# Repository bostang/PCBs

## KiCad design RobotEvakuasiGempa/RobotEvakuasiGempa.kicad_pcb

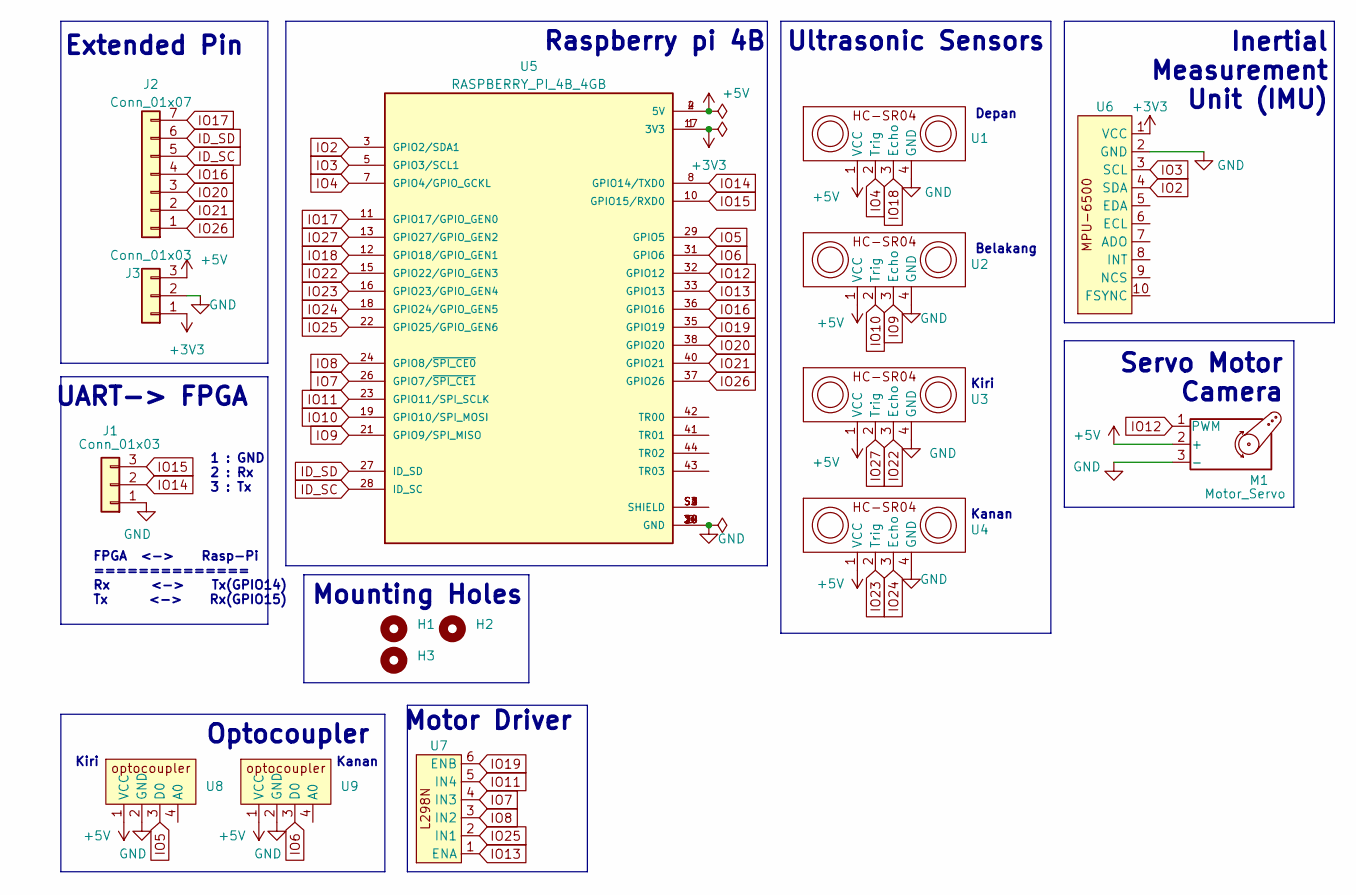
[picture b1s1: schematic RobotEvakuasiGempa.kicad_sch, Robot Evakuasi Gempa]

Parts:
H1, H2, H3: MountingHole; MountingHole_2.2mm_M2
J1, J3: Conn_01x03; PinHeader_1x03_P2.54mm_Vertical
J2: Conn_01x07; PinHeader_1x07_P2.54mm_Vertical
M1: Motor_Servo; PinHeader_1x03_P2.54mm_Vertical
U1, U2, U3, U4: JST_XH_B4B-XH-A_1x04_P2.50mm_Vertical
U5: RASPBERRY_PI_4B_4GB; MODULE_RASPBERRY_PI_4B_4GB_Flat_Ribbon_Cable; PARTREV 4
U6: MPU-6500
U7: L298N
U8, U9: Sensor Optocoupler

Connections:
+3V3: J3.1, U5.1 (3V3), U5.17 (3V3), U6.1 (VCC)
+5V: J3.3, M1.2 (+), U1.1 (VCC), U2.1 (VCC), U3.1 (VCC), U4.1 (VCC), U5.2 (5V), U5.4 (5V), U8.1 (VCC), U9.1 (VCC)
GND: J1.1, J3.2, M1.3 (-), U1.4 (GND), U2.4 (GND), U3.4 (GND), U4.4 (GND), U5.6 (GND), U5.9 (GND), U5.14 (GND), U5.20 (GND), U5.25 (GND), U5.30 (GND), U5.34 (GND), U5.39 (GND), U6.2 (GND), U8.2 (GND), U9.2 (GND)
ID_SC: J2.5, U5.28 (ID_SC)
ID_SD: J2.6, U5.27 (ID_SD)
IO2: U5.3 (GPIO2/SDA1), U6.4 (SDA)
IO3: U5.5 (GPIO3/SCL1), U6.3 (SCL)
IO4: U1.2 (Trig), U5.7 (GPIO4/GPIO_GCKL)
IO5: U5.29 (GPIO5), U8.3 (D0)
IO6: U5.31 (GPIO6), U9.3 (D0)
IO7: U5.26 (GPIO7/~SPI_CE1), U7.4 (IN3)
IO8: U5.24 (GPIO8/~SPI_CE0), U7.3 (IN2)
IO9: U2.3 (Echo), U5.21 (GPIO9/SPI_MISO)
IO10: U2.2 (Trig), U5.19 (GPIO10/SPI_MOSI)
IO11: U5.23 (GPIO11/SPI_SCLK), U7.5 (IN4)
IO12: M1.1 (PWM), U5.32 (GPIO12)
IO13: U5.33 (GPIO13), U7.1 (ENA)
IO14: J1.2, U5.8 (GPIO14/TXD0)
IO15: J1.3, U5.10 (GPIO15/RXD0)
IO16: J2.4, U5.36 (GPIO16)
IO17: J2.7, U5.11 (GPIO17/GPIO_GEN0)
IO18: U1.3 (Echo), U5.12 (GPIO18/GPIO_GEN1)
IO19: U5.35 (GPIO19), U7.6 (ENB)
IO20: J2.3, U5.38 (GPIO20)
IO21: J2.2, U5.40 (GPIO21)
IO22: U3.3 (Echo), U5.15 (GPIO22/GPIO_GEN3)
IO23: U4.2 (Trig), U5.16 (GPIO23/GPIO_GEN4)
IO24: U4.3 (Echo), U5.18 (GPIO24/GPIO_GEN5)
IO25: U5.22 (GPIO25/GPIO_GEN6), U7.2 (IN1)
IO26: J2.1, U5.37 (GPIO26)
IO27: U3.2 (Trig), U5.13 (GPIO27/GPIO_GEN2)

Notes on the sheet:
1 : GND 2 : Rx 3 : Tx
Servo Motor Camera
Mounting Holes
Depan
FPGA <-> Rasp-Pi ============== Rx <-> Tx(GPIO14) Tx <-> Rx(GPIO15)
Kiri
Raspberry pi 4B
UART-> FPGA
Ultrasonic Sensors
Belakang
Motor Driver
Inertial Measurement Unit (IMU)
Kanan
Extended Pin
Optocoupler

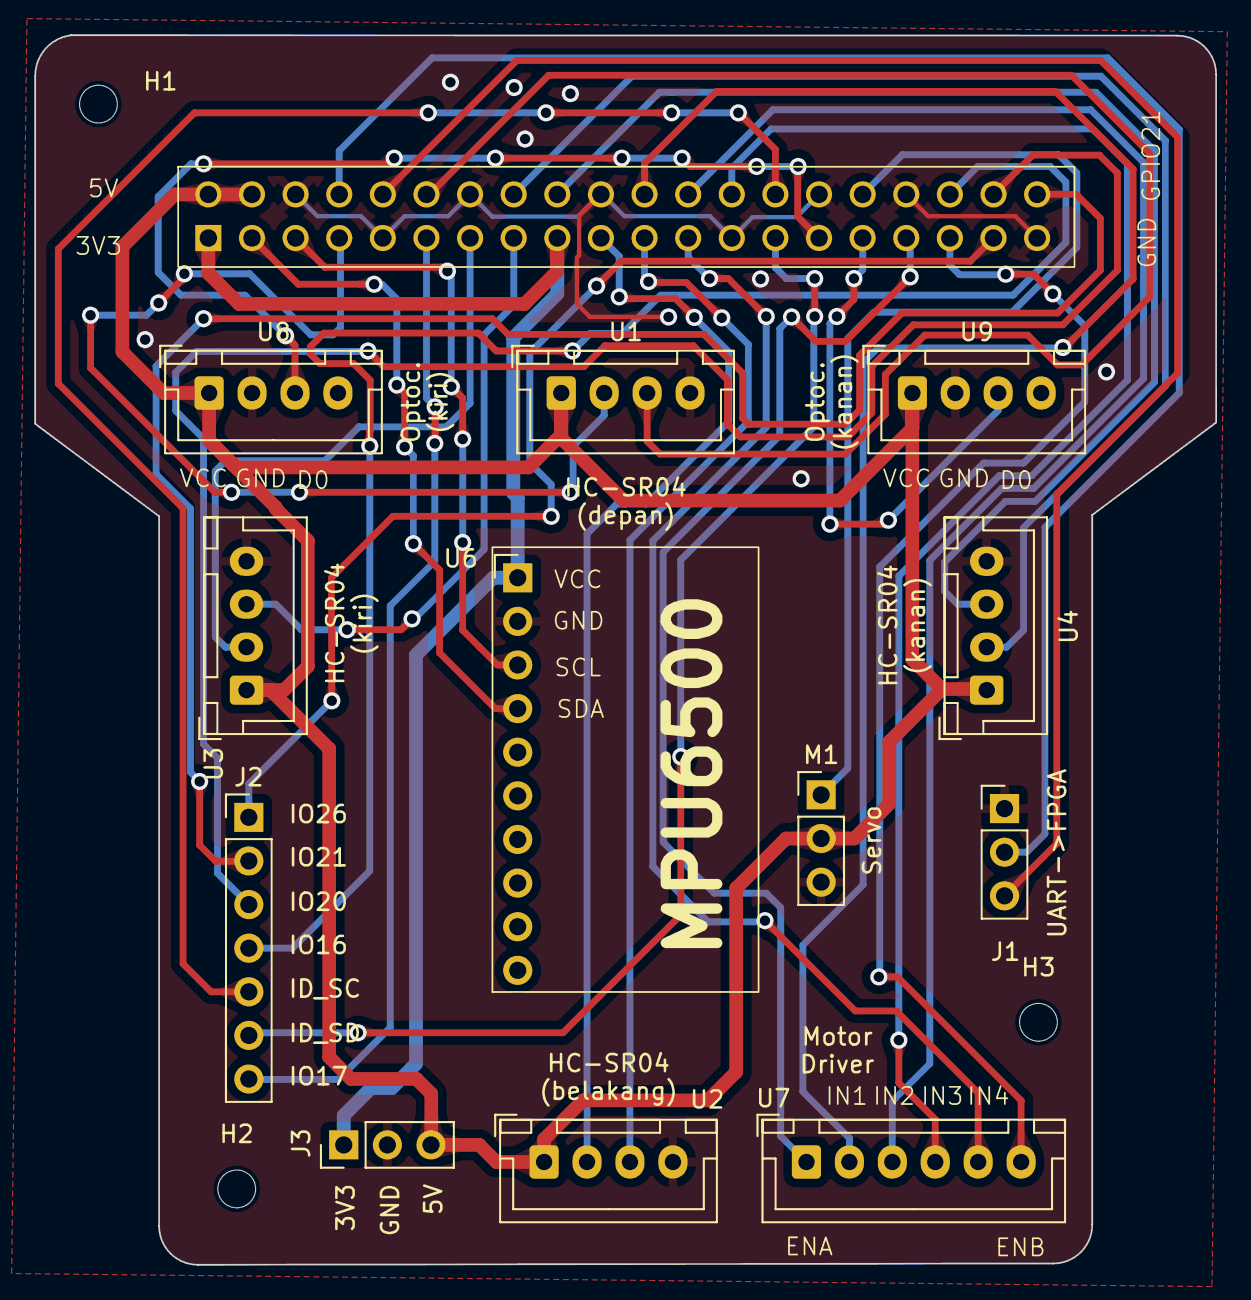
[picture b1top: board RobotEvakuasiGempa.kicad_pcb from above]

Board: 2 copper layers, 68.8 x 71.6 mm, 16 parts (0 on the bottom side), 31 nets.

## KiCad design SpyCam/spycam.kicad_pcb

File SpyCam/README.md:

# Spycam

Sebuah kamera pengintai berbasis ESP-32 camera yang berbentuk sebuah kalung.

# Skematik

# Tampilan

## Tampak Atas

## Tampak Bawah

## Bird-view

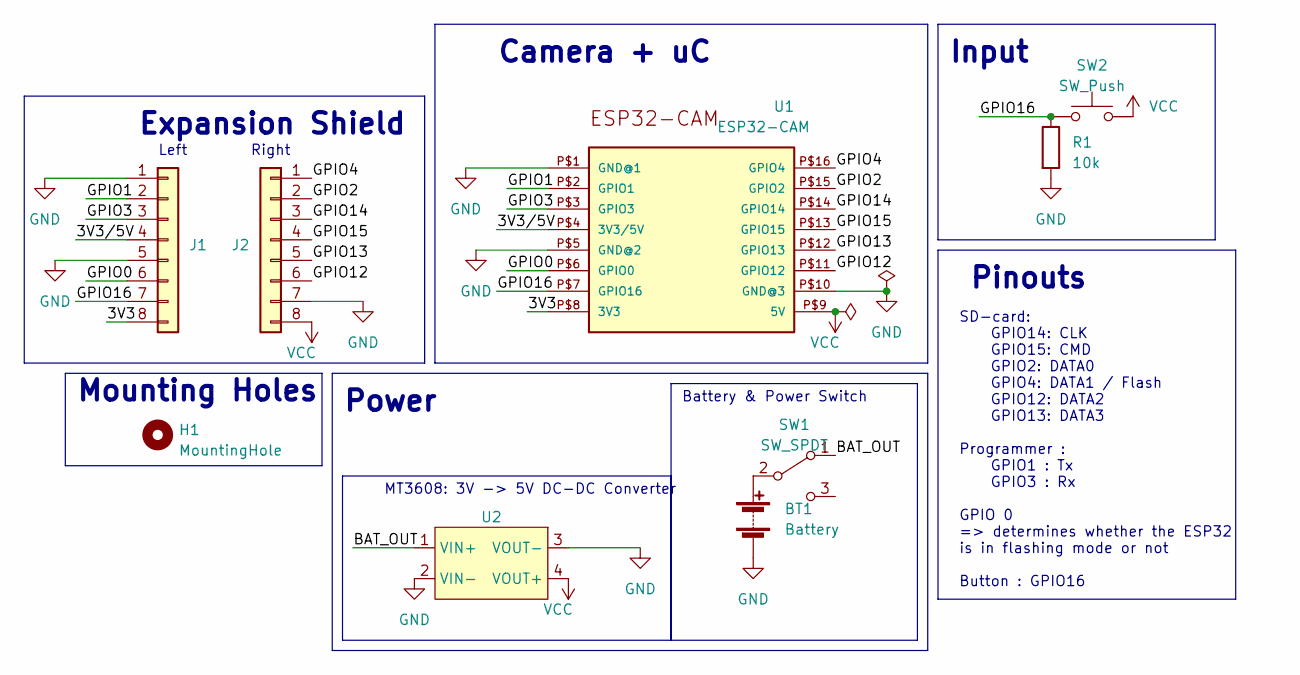
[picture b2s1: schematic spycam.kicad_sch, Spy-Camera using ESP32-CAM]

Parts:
BT1: Battery; BatteryHolder_Keystone_103_1x20mm
H1: MountingHole; MountingHole_3.2mm_M3
J1, J2: Conn_01x08; PinHeader_1x08_P2.54mm_Vertical
R1: 10k; R_1206_3216Metric
SW1: SW_SPDT; SW_E-Switch_EG1224_SPDT_Angled
SW2: SW_Push; SW_PUSH-12mm
U1: ESP32-CAM
U2: MT3608_module_v2

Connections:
/3V3: J1.8, U1.P$8 (3V3)
/3V3/5V: J1.4, U1.P$4 (3V3/5V)
/BAT_OUT: SW1.1 (A), U2.1 (VIN+)
/GPIO0: J1.6, U1.P$6 (GPIO0)
/GPIO1: J1.2, U1.P$2 (GPIO1)
/GPIO2: J2.2, U1.P$15 (GPIO2)
/GPIO3: J1.3, U1.P$3 (GPIO3)
/GPIO4: J2.1, U1.P$16 (GPIO4)
/GPIO12: J2.6, U1.P$11 (GPIO12)
/GPIO13: J2.5, U1.P$12 (GPIO13)
/GPIO14: J2.3, U1.P$14 (GPIO14)
/GPIO15: J2.4, U1.P$13 (GPIO15)
/GPIO16: J1.7, R1.1, SW2.1, U1.P$7 (GPIO16)
GND: BT1.2 (-), J1.1, J1.5, J2.7, R1.2, U1.P$1 (GND@1), U1.P$5 (GND@2), U1.P$10 (GND@3), U2.2 (VIN-), U2.3 (VOUT-)
unnamed: BT1.1 (+), SW1.2 (B)
VCC: J2.8, SW2.2, U1.P$9 (5V), U2.4 (VOUT+)

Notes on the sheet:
Expansion Shield
MT3608: 3V -> 5V DC-DC Converter
Pinouts
Battery & Power Switch
Right
Left
SD-card: GPIO14: CLK GPIO15: CMD GPIO2: DATA0 GPIO4: DATA1 / Flash GPIO12: DATA2 GPIO13: DATA3 Programmer : GPIO1 : Tx GPIO3 : Rx GPIO 0 => determines whether the ESP32 is in flashing mode or not Button : GPIO16
Mounting Holes
Camera + uC
Input
Power

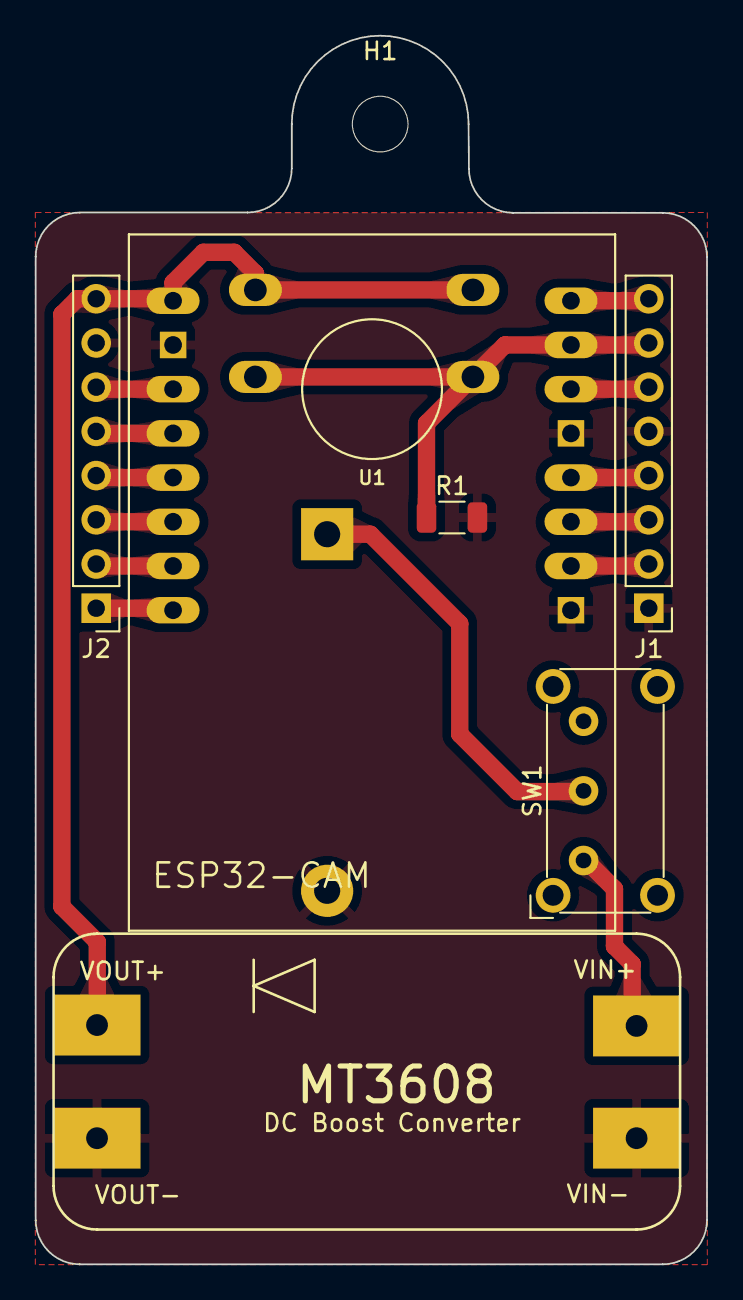
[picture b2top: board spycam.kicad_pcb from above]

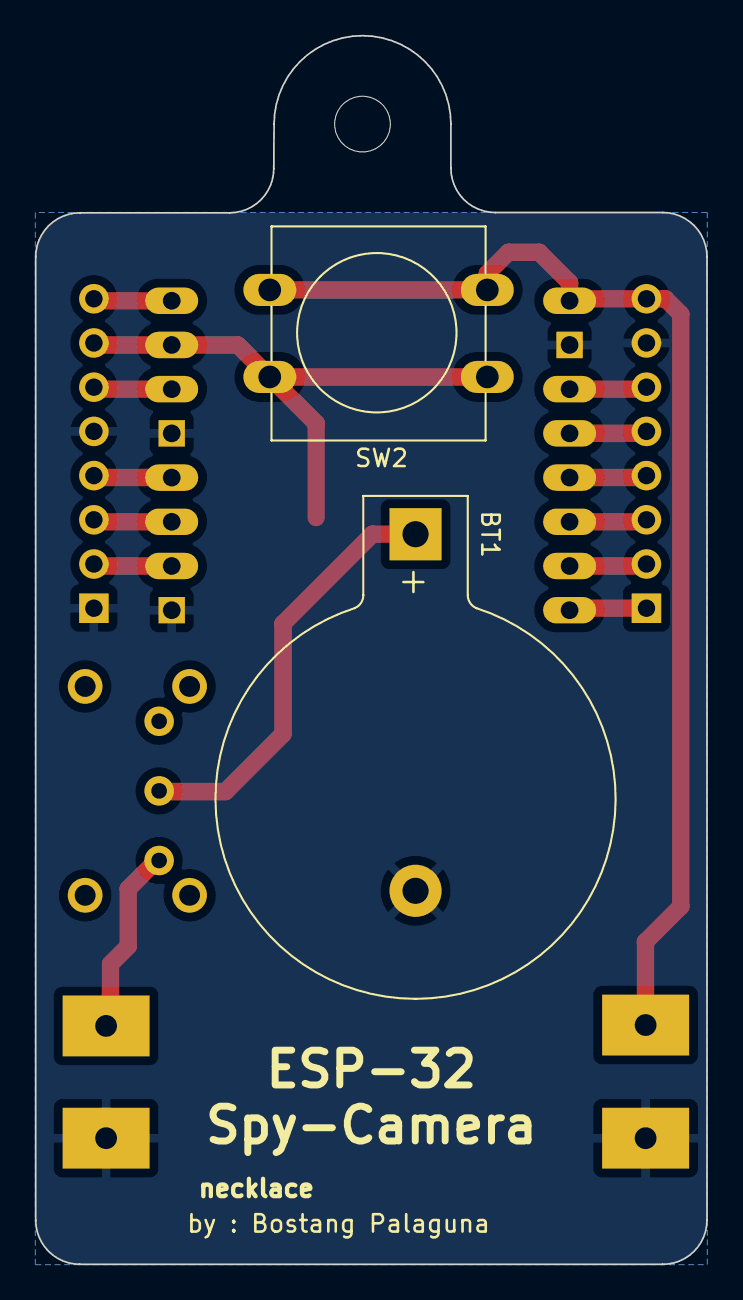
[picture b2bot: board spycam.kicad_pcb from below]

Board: 2 copper layers, 38.6 x 70.6 mm, 9 parts (2 on the bottom side), 16 nets.

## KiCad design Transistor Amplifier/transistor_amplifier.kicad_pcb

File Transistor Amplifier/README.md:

# Transistor Amplifier

Rangkaian Penguat kelas A menggunakan dua buah transistor BJT (konfigurasi common emitter (CE) cascade dengan common collector (CC) untuk tugas besar EL2205 Praktikum Elektronika (first made 2022, but with bad design. recreated 2024).

# Skematik

# Tampilan

## Tampak Atas

## Tampak Bawah

## Bird-view

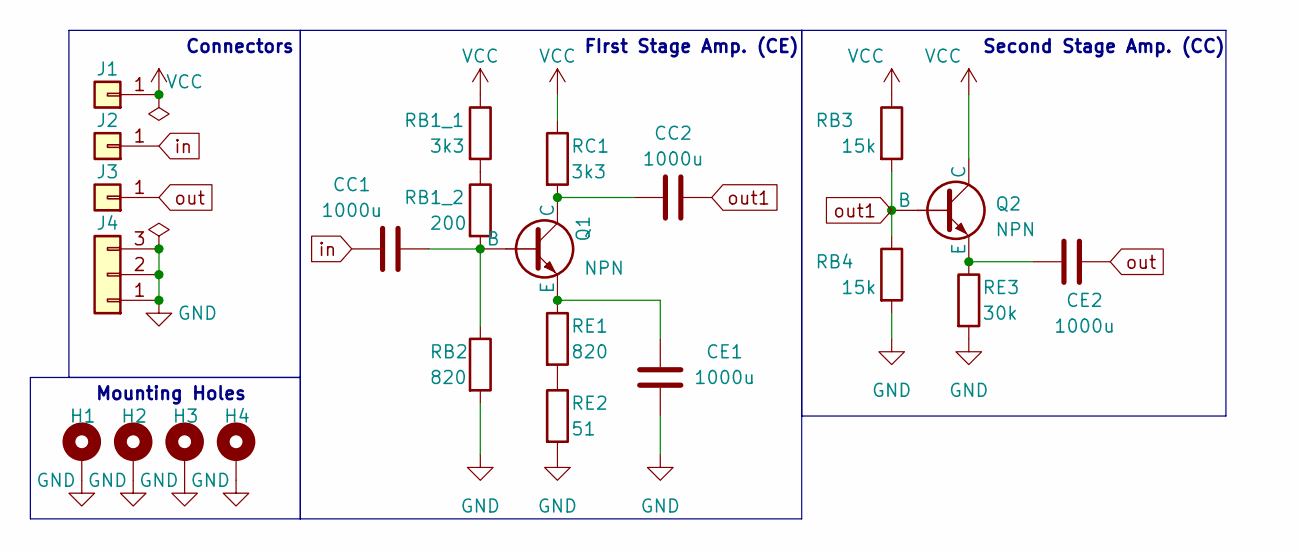
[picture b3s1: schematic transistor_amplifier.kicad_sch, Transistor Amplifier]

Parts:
CC1, CC2: 1000u; CP_Elec_10x10
CE1, CE2: 1000u; CP_Elec_10x10
H1, H2, H3, H4: MountingHole_Pad; MountingHole_2.2mm_M2_Pad_Via
J1, J2, J3: Conn_01x01; Banana_Jack_1Pin
J4: Conn_01x03; Banana_Jack_3Pin
Q1, Q2: NPN; TO-92_Inline
RB1_1: 3k3; R_0805_2012Metric
RB1_2: 200; R_0805_2012Metric
RB2: 820; R_0805_2012Metric
RB3, RB4: 15k; R_0805_2012Metric
RC1: 3k3; R_0805_2012Metric
RE1: 820; R_0805_2012Metric
RE2: 51; R_0805_2012Metric
RE3: 30k; R_0805_2012Metric

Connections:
GND: CE1.1, H1.1, H2.1, H3.1, H4.1, J4.1, J4.2, J4.3, RB2.2, RB4.2, RE2.2, RE3.2
unnamed: CC1.2, Q1.2 (B), RB1_2.2, RB2.1
unnamed: CC2.1, Q1.1 (C), RC1.2
unnamed: CE1.2, Q1.3 (E), RE1.1
unnamed: CE2.2, Q2.3 (E), RE3.1
unnamed: RB1_1.2, RB1_2.1
unnamed: RE1.2, RE2.1
VCC: J1.1, Q2.1 (C), RB1_1.1, RB3.1, RC1.1
in: CC1.1, J2.1
out: CE2.1, J3.1
out1: CC2.2, Q2.2 (B), RB3.2, RB4.1

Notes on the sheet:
Second Stage Amp. (CC)
Mounting Holes
FIrst Stage Amp. (CE)
Connectors

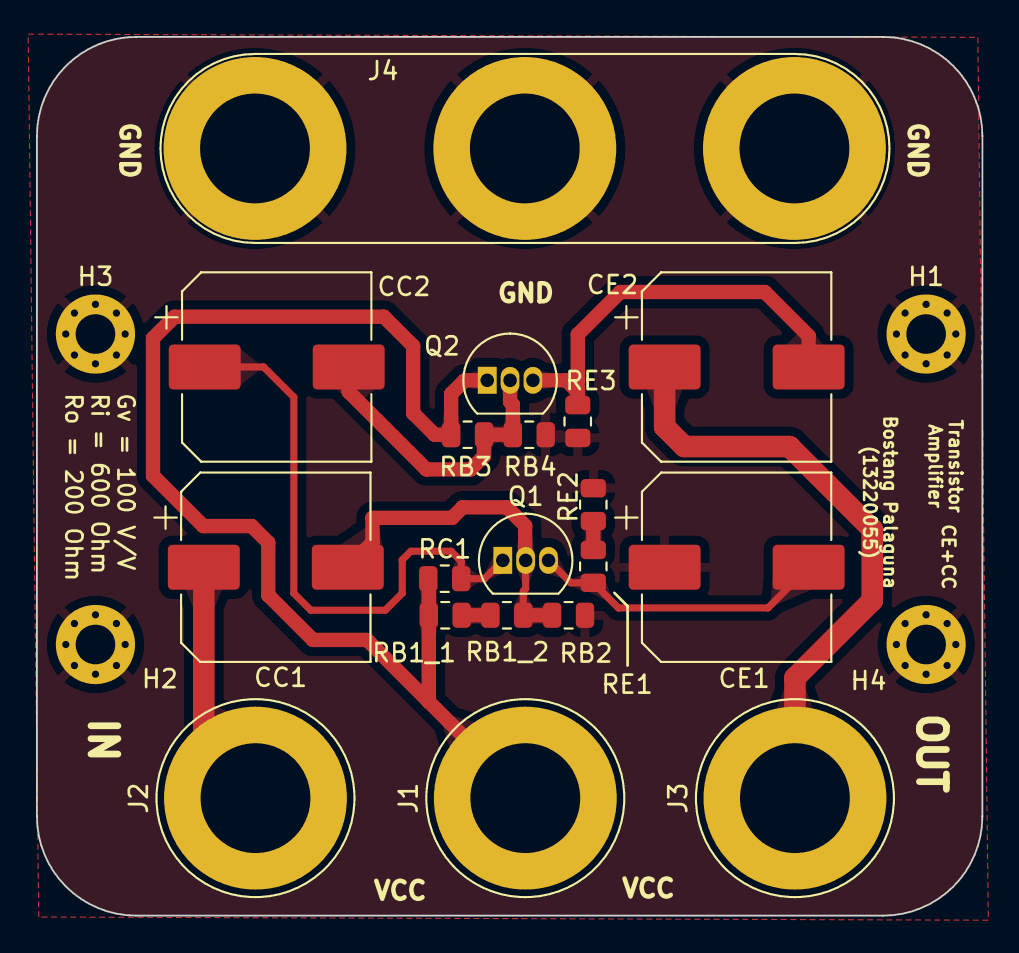
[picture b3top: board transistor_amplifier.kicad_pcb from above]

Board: 2 copper layers, 52.5 x 48.8 mm, 23 parts (0 on the bottom side), 11 nets.

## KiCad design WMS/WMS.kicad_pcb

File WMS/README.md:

# WMS Scanner

Sebuah perangkat genggam (hand-held device) untuk melakukan scanning kode barang dengan dua mode : barcode dan juga RFID. Proyek ini adalah bagian dari tugas akhir saya

# Skematik

## Top-level

## Sub-sistem : Data Acquisition

## Sub-sistem : Data Processing & Gateway

## Sub-sistem : Display

## Sub-sistem : Power

# Tampilan 3D

## V4

### Tampak Atas

### Tampak Bawah

### Bird-view

## V3

### Tampak Atas

### Tampak Bawah

### Bird-view

# Catatan Perbaikan PCB v4
## v4.0
Berikut adalah beberapa perbaikan yang dilakukan dari PCB v3 ke v4 :
-	PCB dibuat dalam 4 Layer (signal-PWR-GND-signal) untuk mengurangi electromagnetic interference (EMI).
-	Menggunakan banyak kapasitor decoupling untuk mengurangi noise frekuensi tinggi dan rendah.
-	Menggunakan hardware debouncer (Schmitt Trigger + R, C) untuk ketiga push button yang akan rutin ditekan oleh user.
-	Bagian PCB (shield) yang tersambung dengan Antenna PSoC dibuat terbuka untuk meminimialkan masalah jaringan (antenna isolation).
-	Penambahan testing points untuk sinyal-sinyal (Tx-Rx Barcode, RFID, tegangan baterai, dan tegangan keluaran regulator tegangan) untuk debugging.
-	Pengurangan Silkscreen terhadap informasi yang berlebihan dan tidak perlu.
-	Mengubah footprint modul RFID pada bagaian konektor: FPC + solder pad (sebelumnya FPC saja).
-	Penambahan beberapa dioda proteksi (wheeler diode) untuk mencegah spike tegangan saat sakelar power ataupun sakelar barcode-RFID berubah keadaan.
-	Penambahan jumlah mounting hole sebanyak dua buah lagi di titik-titik PCB yang tidak ramai.

## v4.1
-  Memberikan clearance ujung PCB (tidak boleh ada copper plane atau track) minimal 1 mm dari ujung. ==> rawan short di bagian ujung. 
- Setiap berpindah layer menggunakan via, dipasangkan dengan via menuju GND. ==> high speed PCB untuk mengurangi EMI. 
- Memperlebar sedikit ujung papan PCB untuk mengurangi pengaruh medan elektromagnetik di ujung edge effect. (medan menyebar di forth path dan return path di bawah trace. Signal reflection. 
- Memaksimalkan jarak-jarak antar dua track yang parallel untuk mengurangi cross-talk.

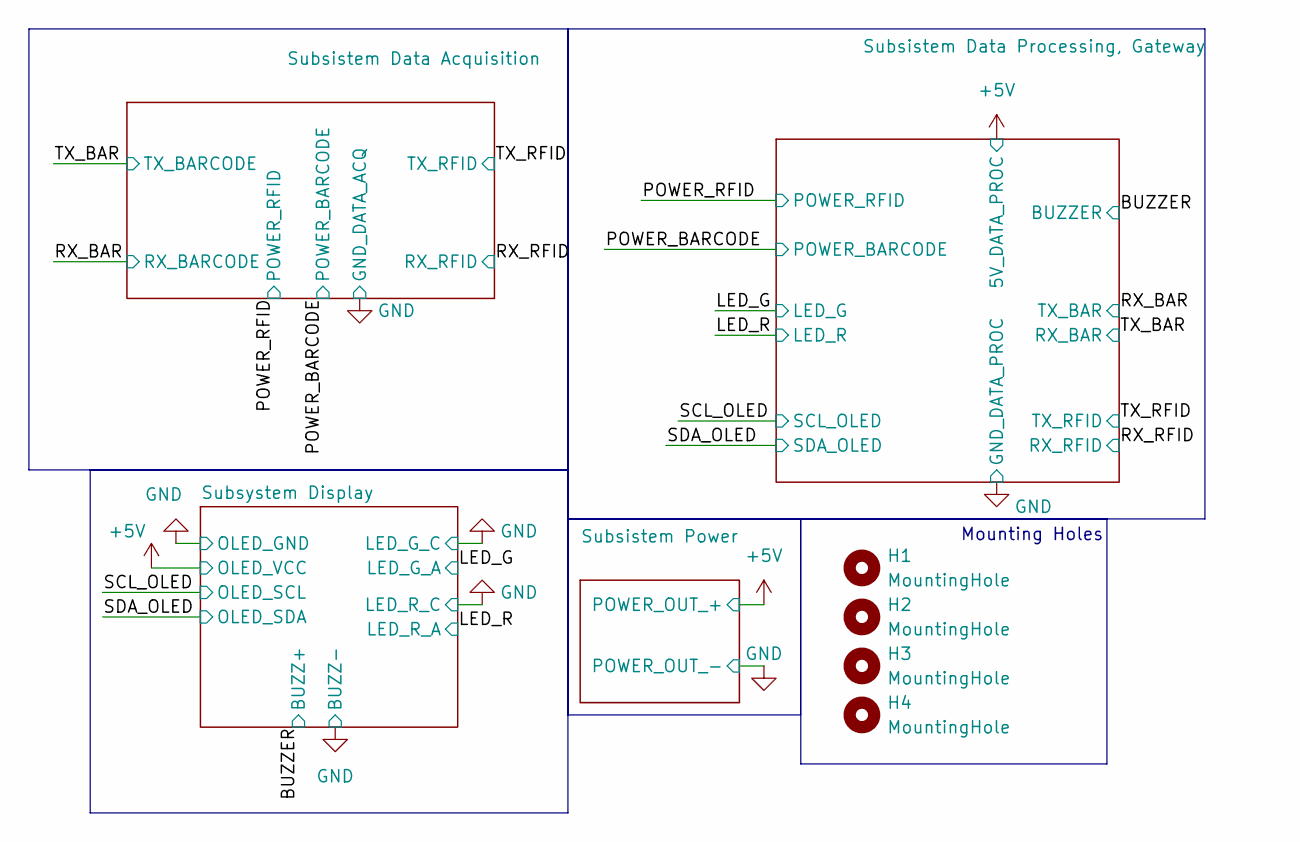
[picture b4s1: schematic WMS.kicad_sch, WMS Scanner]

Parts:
H1, H2, H3, H4: MountingHole; MountingHole_2.2mm_M2

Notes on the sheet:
Mounting Holes

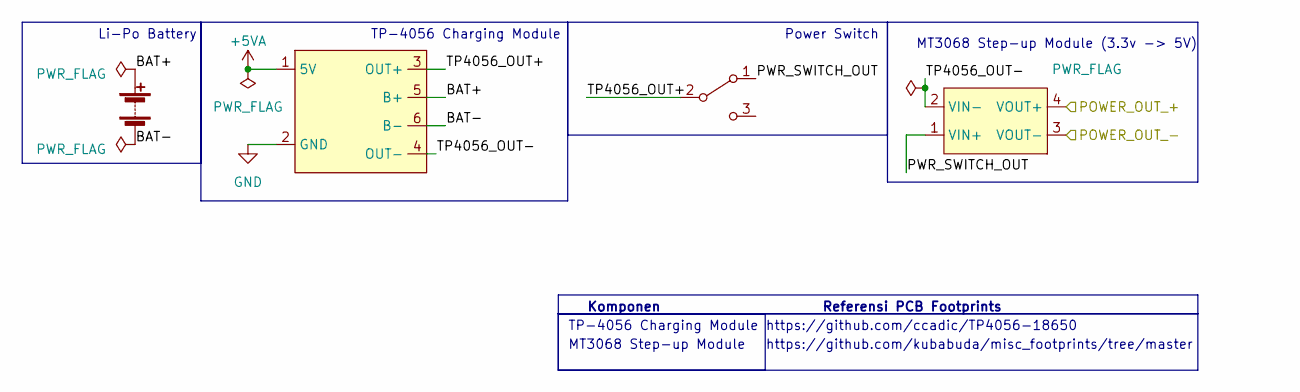
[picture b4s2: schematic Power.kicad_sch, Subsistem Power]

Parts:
BT1: Battery; BatteryHolder_Keystone_1042_1x18650
SW4: SW_SPDT; SPDT
U2: TP4056-18650_v2
U3: MT3608_module_v2

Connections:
+5V: U3.4 (VOUT+); also elsewhere on the board
+5VA: U2.1 (5V)
/Subsistem Power/BAT+: BT1.1 (+), U2.5 (B+)
/Subsistem Power/BAT-: BT1.2 (-), U2.6 (B-)
/Subsistem Power/PWR_SWITCH_OUT: SW4.1 (A), U3.1 (VIN+)
/Subsistem Power/TP4056_OUT+: SW4.2 (B), U2.3 (OUT+)
/Subsistem Power/TP4056_OUT-: U2.4 (OUT-), U3.2 (VIN-)
GND: U2.2 (GND), U3.3 (VOUT-); also elsewhere on the board

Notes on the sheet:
https://github.com/ccadic/TP4056-18650
https://github.com/kubabuda/misc_footprints/tree/master
TP-4056 Charging Module
Li-Po Battery
Komponen
MT3068 Step-up Module
Power Switch
Referensi PCB Footprints
MT3068 Step-up Module (3.3v -> 5V)

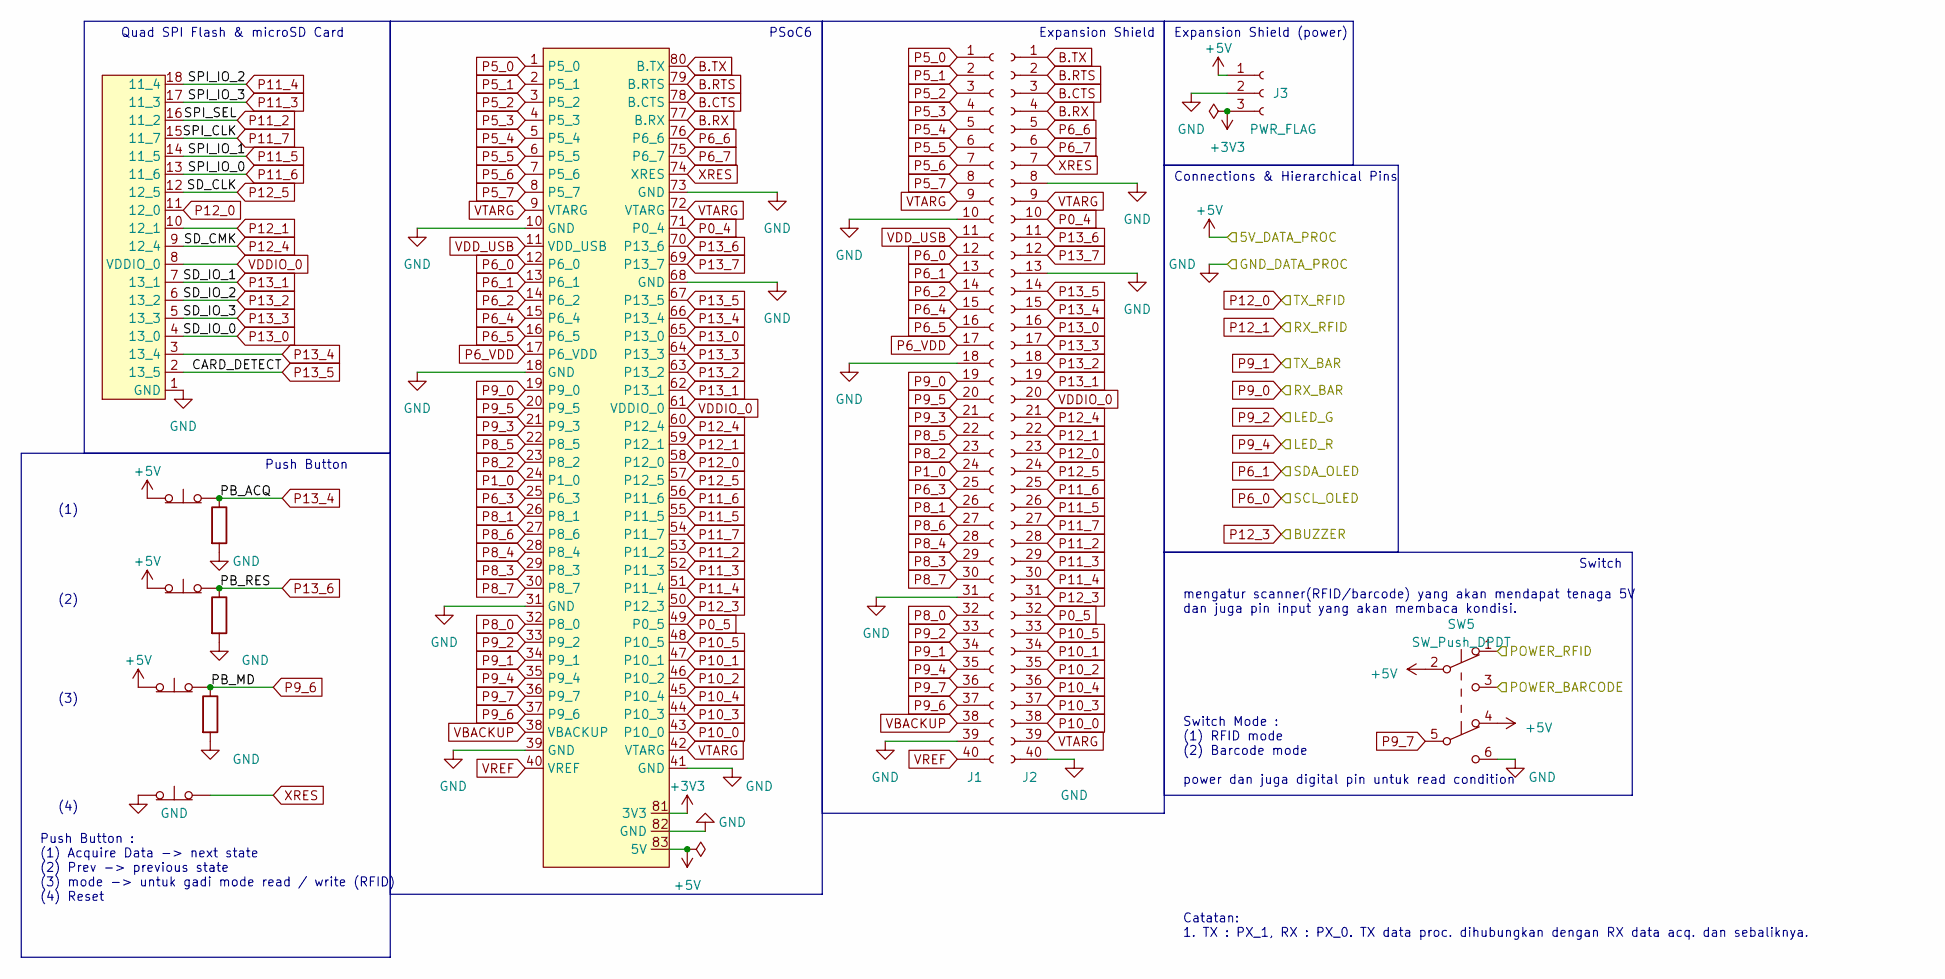
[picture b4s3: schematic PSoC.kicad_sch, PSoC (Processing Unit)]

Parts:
J1, J2: Conn_01x40_Socket; PinHeader_1x40_P2.54mm_Vertical
J3: Conn_01x03_Socket; PinHeader_1x03_P2.54mm_Vertical
R3, R4, R5: 10k; R_0805_2012Metric
SW1, SW2, SW3: SW_Push_Open; SW_PUSH-12mm
SW5: SW_Push_DPDT; DPDT
SW6: SW_Push_Open; SW_PUSH_6mm_H9.5mm
U5: Quad_SPI_flash_microSD_v2
U6: CY8CPROTO-062-4343W_v3

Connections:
+3V3: J3.3, U6.81 (3V3)
+5V: J3.1, SW1.1 (A), SW2.1 (A), SW3.1 (A), SW5.2 (B), SW5.4 (A), U6.83 (5V); also elsewhere on the board
/POWER_BARCODE: SW5.3 (C); also elsewhere on the board
/POWER_RFID: SW5.1 (A); also elsewhere on the board
B.CTS: J2.3, U6.78 (B.CTS)
B.RTS: J2.2, U6.79 (B.RTS)
B.RX: J2.4, U6.77 (B.RX)
B.TX: J2.1, U6.80 (B.TX)
GND: J1.10, J1.18, J1.31, J1.39, J2.8, J2.13, J2.40, J3.2, R3.2, R4.2, R5.2, SW5.6 (C), SW6.1 (A), U5.1 (GND), U6.10 (GND), U6.18 (GND), U6.31 (GND), U6.39 (GND), U6.41 (GND), U6.68 (GND), U6.73 (GND), U6.82 (GND); also elsewhere on the board
P0_4: J2.10, U6.71 (P0_4)
P0_5: J2.32, U6.49 (P0_5)
P1_0: J1.24, U6.24 (P1_0)
P5_0: J1.1, U6.1 (P5_0)
P5_1: J1.2, U6.2 (P5_1)
P5_2: J1.3, U6.3 (P5_2)
P5_3: J1.4, U6.4 (P5_3)
P5_4: J1.5, U6.5 (P5_4)
P5_5: J1.6, U6.6 (P5_5)
P5_6: J1.7, U6.7 (P5_6)
P5_7: J1.8, U6.8 (P5_7)
P6_0: J1.12, U6.12 (P6_0); also elsewhere on the board
P6_1: J1.13, U6.13 (P6_1); also elsewhere on the board
P6_2: J1.14, U6.14 (P6_2)
P6_3: J1.25, U6.25 (P6_3)
P6_4: J1.15, U6.15 (P6_4)
P6_5: J1.16, U6.16 (P6_5)
P6_6: J2.5, U6.76 (P6_6)
P6_7: J2.6, U6.75 (P6_7)
P6_VDD: J1.17, U6.17 (P6_VDD)
P8_0: J1.32, U6.32 (P8_0)
P8_1: J1.26, U6.26 (P8_1)
P8_2: J1.23, U6.23 (P8_2)
P8_3: J1.29, U6.29 (P8_3)
P8_4: J1.28, U6.28 (P8_4)
P8_5: J1.22, U6.22 (P8_5)
P8_6: J1.27, U6.27 (P8_6)
P8_7: J1.30, U6.30 (P8_7)
P9_0: J1.19, U6.19 (P9_0); also elsewhere on the board
P9_1: J1.34, U6.34 (P9_1); also elsewhere on the board
P9_2: J1.33, U6.33 (P9_2); also elsewhere on the board
P9_3: J1.21, U6.21 (P9_3)
P9_4: J1.35, U6.35 (P9_4); also elsewhere on the board
P9_5: J1.20, U6.20 (P9_5)
P9_6: J1.37, R5.1, SW3.2 (B), U6.37 (P9_6)
P9_7: J1.36, SW5.5 (B), U6.36 (P9_7)
P10_0: J2.38, U6.43 (P10_0)
P10_1: J2.34, U6.47 (P10_1)
P10_2: J2.35, U6.46 (P10_2)
P10_3: J2.37, U6.44 (P10_3)
P10_4: J2.36, U6.45 (P10_4)
P10_5: J2.33, U6.48 (P10_5)
P11_2: J2.28, U5.16 (11_2), U6.53 (P11_2)
P11_3: J2.29, U5.17 (11_3), U6.52 (P11_3)
P11_4: J2.30, U5.18 (11_4), U6.51 (P11_4)
P11_5: J2.26, U5.14 (11_5), U6.55 (P11_5)
P11_6: J2.25, U5.13 (11_6), U6.56 (P11_6)
P11_7: J2.27, U5.15 (11_7), U6.54 (P11_7)
P12_0: J2.23, U5.11 (12_0), U6.58 (P12_0); also elsewhere on the board
P12_1: J2.22, U5.10 (12_1), U6.59 (P12_1); also elsewhere on the board
P12_3: J2.31, U6.50 (P12_3); also elsewhere on the board
P12_4: J2.21, U5.9 (12_4), U6.60 (P12_4)
P12_5: J2.24, U5.12 (12_5), U6.57 (P12_5)
P13_0: J2.16, U5.4 (13_0), U6.65 (P13_0)
P13_1: J2.19, U5.7 (13_1), U6.62 (P13_1)
P13_2: J2.18, U5.6 (13_2), U6.63 (P13_2)
P13_3: J2.17, U5.5 (13_3), U6.64 (P13_3)
P13_4: J2.15, R3.1, SW1.2 (B), U5.3 (13_4), U6.66 (P13_4)
P13_5: J2.14, U5.2 (13_5), U6.67 (P13_5)
P13_6: J2.11, R4.1, SW2.2 (B), U6.70 (P13_6)
P13_7: J2.12, U6.69 (P13_7)
VBACKUP: J1.38, U6.38 (VBACKUP)
VDDIO_0: J2.20, U5.8 (VDDIO_0), U6.61 (VDDIO_0)
VDD_USB: J1.11, U6.11 (VDD_USB)
VREF: J1.40, U6.40 (VREF)
VTARG: J1.9, J2.9, J2.39, U6.9 (VTARG), U6.42 (VTARG), U6.72 (VTARG)
XRES: J2.7, SW6.2 (B), U6.74 (XRES)

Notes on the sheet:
(3)
PSoC6
Expansion Shield (power)
(2)
(4)
Push Button : (1) Acquire Data -> next state (2) Prev -> previous state (3) mode -> untuk gadi mode read / write (RFID) (4) Reset
(1)
Switch
Expansion Shield
Connections & Hierarchical Pins
mengatur scanner(RFID/barcode) yang akan mendapat tenaga 5V dan juga pin input yang akan membaca kondisi.
Catatan: 1. TX : PX_1, RX : PX_0. TX data proc. dihubungkan dengan RX data acq. dan sebaliknya.
Switch Mode : (1) RFID mode (2) Barcode mode power dan juga digital pin untuk read condition
Quad SPI Flash & microSD Card
Push Button

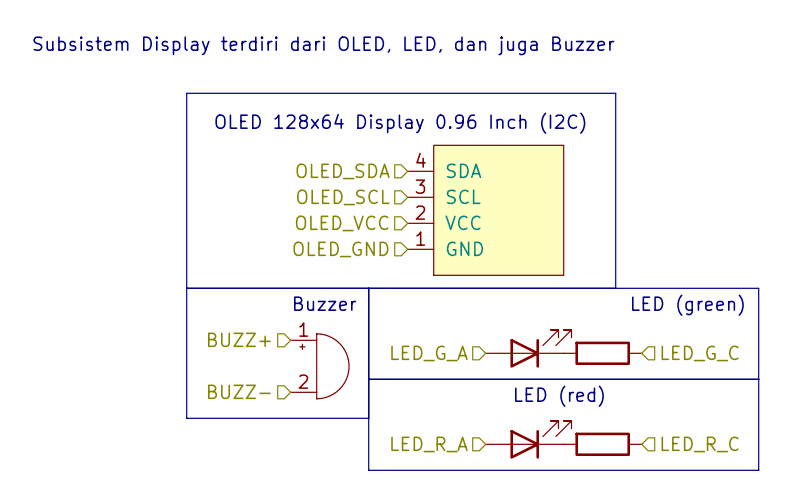
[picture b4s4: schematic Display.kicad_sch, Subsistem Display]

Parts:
BZ1: Buzzer; Buzzer_12x9.5RM7.6
Brd1: SSD1306; 128x64OLED
D1, D2: LED; LED_D3.0mm
R1: 82; R_0805_2012Metric
R2: 120; R_0805_2012Metric

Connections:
+5V: Brd1.2 (VCC); also elsewhere on the board
GND: BZ1.2 (+), Brd1.1 (GND), R1.1, R2.1; also elsewhere on the board
unnamed: D1.1 (K), R1.2
unnamed: D2.1 (K), R2.2
P6_0: Brd1.3 (SCL); also elsewhere on the board
P6_1: Brd1.4 (SDA); also elsewhere on the board
P9_2: D1.2 (A); also elsewhere on the board
P9_4: D2.2 (A); also elsewhere on the board
P12_3: BZ1.1 (-); also elsewhere on the board

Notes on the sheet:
Subsistem Display terdiri dari OLED, LED, dan juga Buzzer
LED (red)
Buzzer
OLED 128x64 Display 0.96 Inch (I2C)
LED (green)

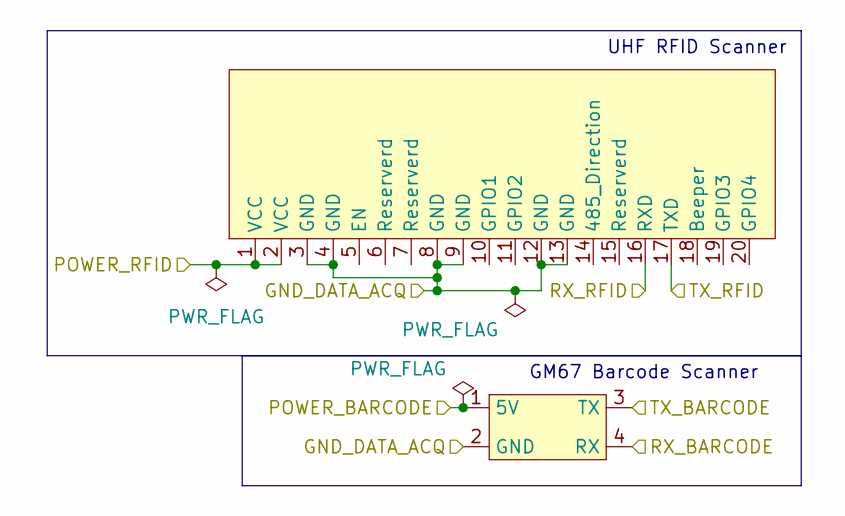
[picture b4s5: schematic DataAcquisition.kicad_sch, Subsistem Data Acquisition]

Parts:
U1: YR903_RFID_Scanner_FPC_v2
U4: JST_SH_SM04B-SRSS-TB_1x04-1MP_P1.00mm_Horizontal

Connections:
/POWER_BARCODE: U4.1 (5V); also elsewhere on the board
/POWER_RFID: U1.1 (VCC), U1.2 (VCC); also elsewhere on the board
GND: U1.3 (GND), U1.4 (GND), U1.8 (GND), U1.9 (GND), U1.12 (GND), U1.13 (GND), U4.2 (GND); also elsewhere on the board
P9_0: U4.3 (TX); also elsewhere on the board
P9_1: U4.4 (RX); also elsewhere on the board
P12_0: U1.17 (TXD); also elsewhere on the board
P12_1: U1.16 (RXD); also elsewhere on the board

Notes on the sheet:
UHF RFID Scanner
GM67 Barcode Scanner

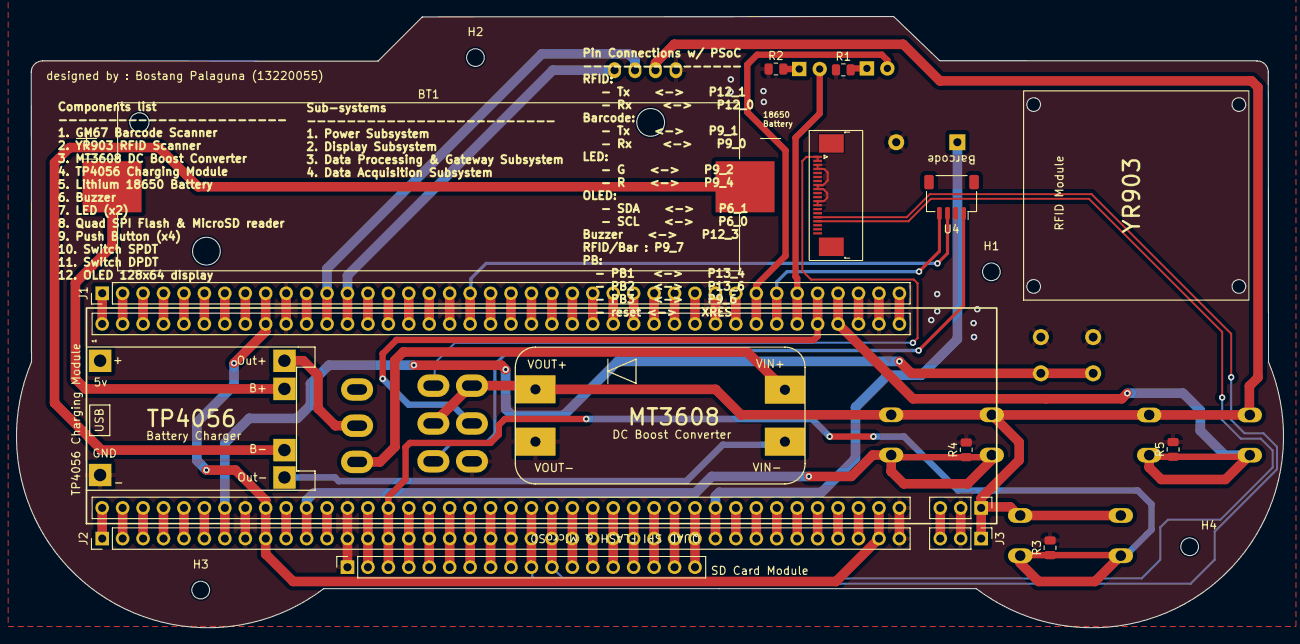
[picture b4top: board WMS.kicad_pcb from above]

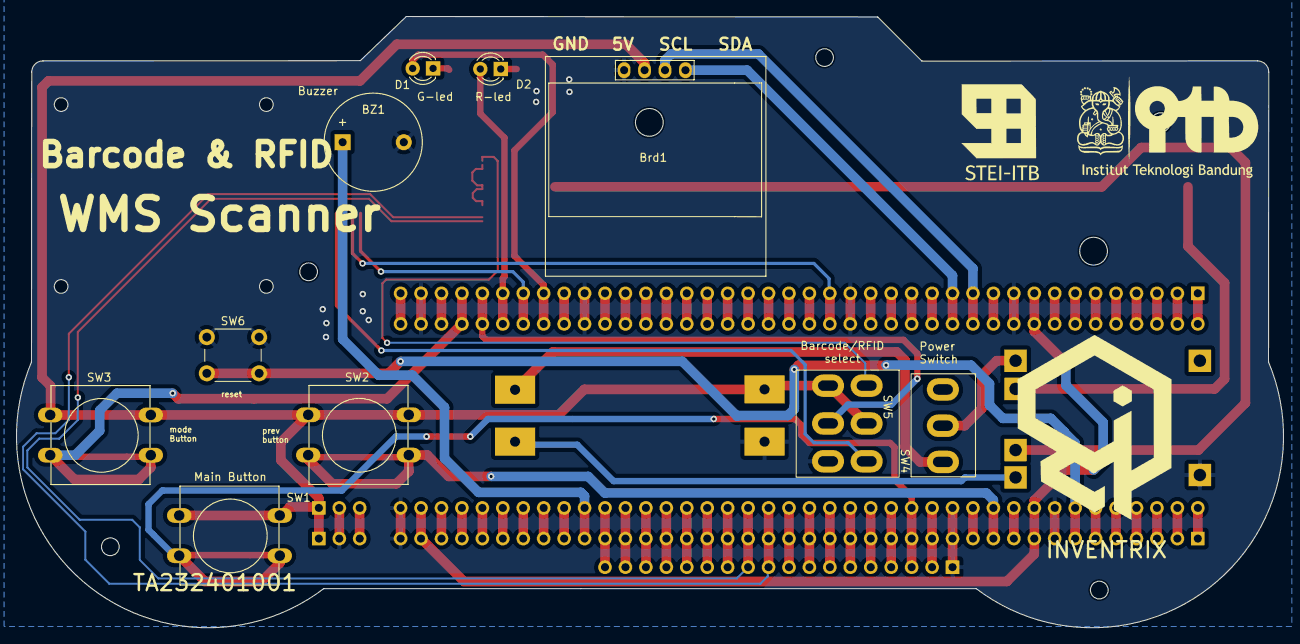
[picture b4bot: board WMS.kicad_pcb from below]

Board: 2 copper layers, 157.4 x 75.9 mm, 29 parts (10 on the bottom side), 83 nets.
